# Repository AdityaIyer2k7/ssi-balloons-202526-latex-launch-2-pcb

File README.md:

# Stanford SSI Balloons; 2025-26 Latex Launch 2; PCB

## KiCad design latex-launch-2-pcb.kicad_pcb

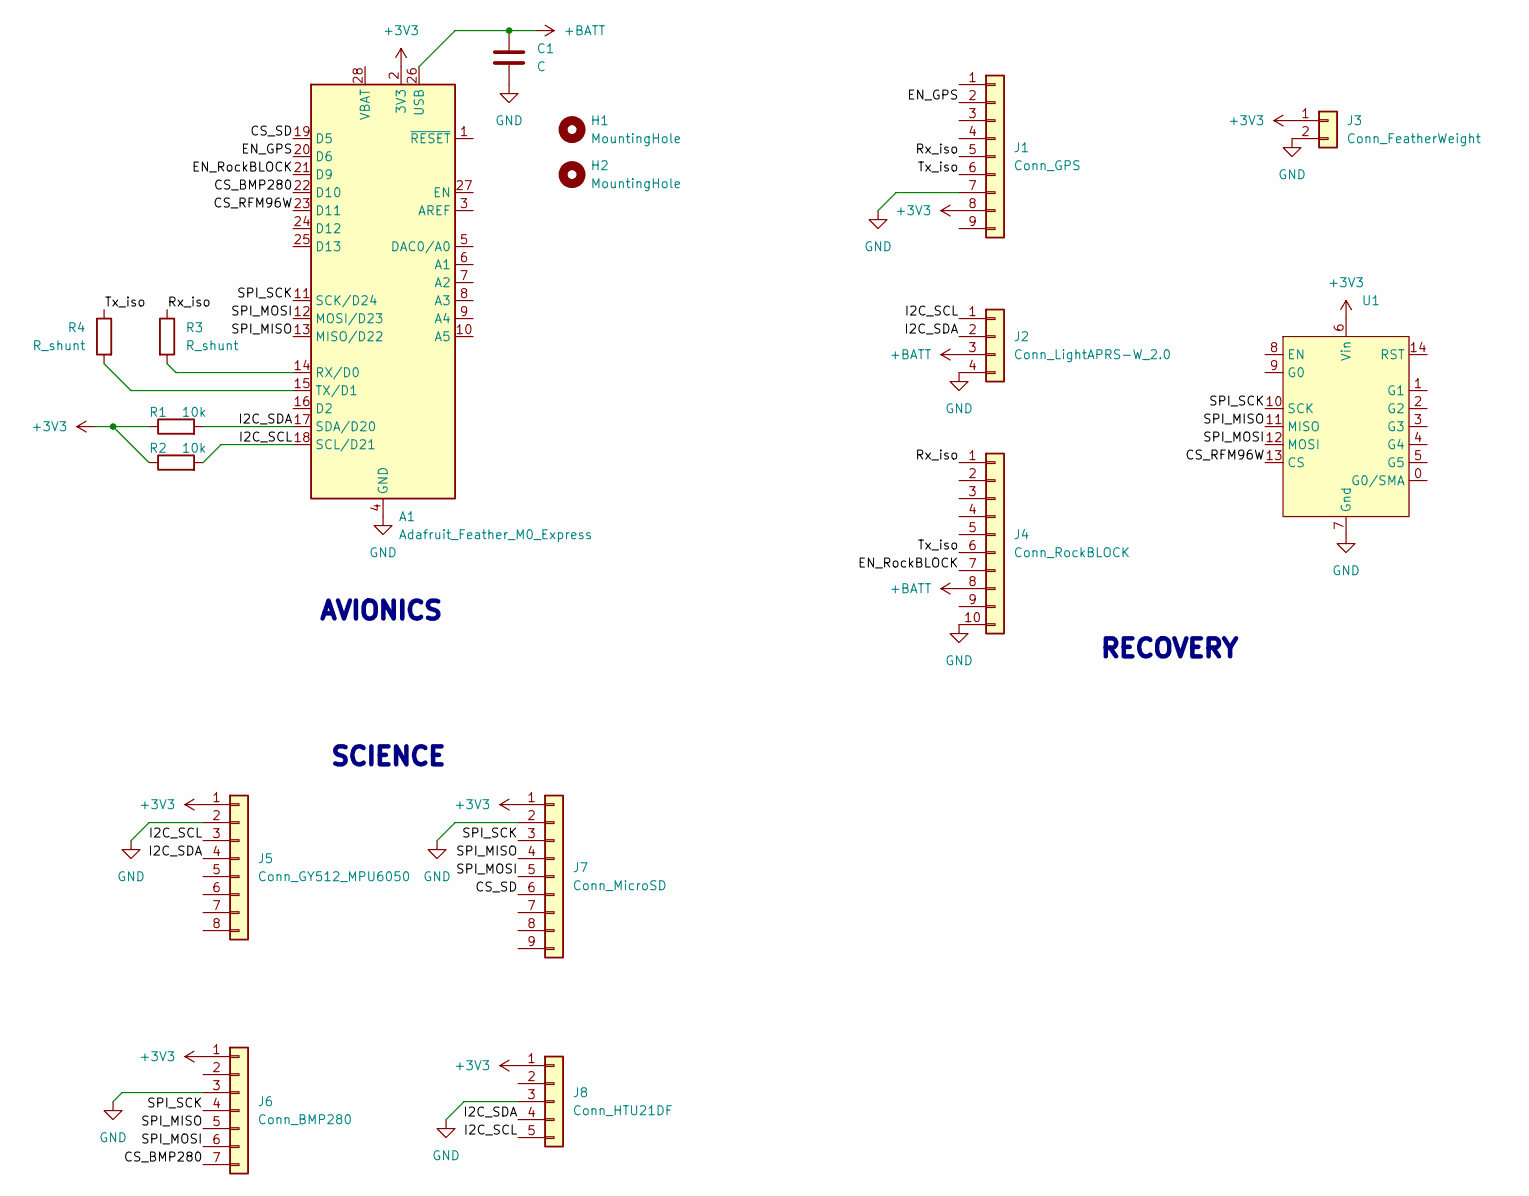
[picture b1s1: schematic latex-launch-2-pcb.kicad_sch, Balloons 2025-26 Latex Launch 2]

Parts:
A1: Adafruit_Feather_M0_Express; Adafruit_Feather_M0_RFM_WithMountingHoles
C1: C; C_Rect_L4.6mm_W2.0mm_P2.50mm_MKS02_FKP02
H1, H2: MountingHole; MountingHole_2.7mm_M2.5_ISO7380_Pad
J1: Conn_GPS; Adafruit_GPS_Breakout
J2: Conn_LightAPRS-W_2.0; JST_PH_S4B-PH-SM4-TB_1x04-1MP_P2.00mm_Horizontal
J3: Conn_FeatherWeight; JST_PH_S2B-PH-SM4-TB_1x02-1MP_P2.00mm_Horizontal
J4: Conn_RockBLOCK; Molex_PicoBlade_53047-1010_1x10_P1.25mm_Vertical
J5: Conn_GY512_MPU6050; GY-521 MPU6050
J6: Conn_BMP280; Adafruit_BMP280_Breakout
J7: Conn_MicroSD; Adafruit_MicroSD_Breakout
J8: Conn_HTU21DF; Adafruit_HTU21DF_Breakout
R1, R2: 10k; R_Axial_DIN0207_L6.3mm_D2.5mm_P10.16mm_Horizontal
R3, R4: R_shunt; PinHeader_1x02_P2.54mm_Vertical
U1: Adafruit_RFM96W_LoRa_Breakout

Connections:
+3V3: A1.2 (3V3), J1.8, J3.1, J5.1, J6.1, J7.1, J8.1, R1.1, R2.1, U1.6 (Vin)
+BATT: A1.26 (USB), C1.1, J2.3, J4.8
/CS_BMP280: A1.22 (D10), J6.7
/CS_RFM96W: A1.23 (D11), U1.13 (CS)
/CS_SD: A1.19 (D5), J7.6
/EN_GPS: A1.20 (D6), J1.2
/EN_RockBLOCK: A1.21 (D9), J4.7
/I2C_SCL: A1.18 (SCL/D21), J2.1, J5.3, J8.5, R2.2
/I2C_SDA: A1.17 (SDA/D20), J2.2, J5.4, J8.4, R1.2
/Rx_iso: J1.5, J4.1, R3.1
/SPI_MISO: A1.13 (MISO/D22), J6.5, J7.4, U1.11 (MISO)
/SPI_MOSI: A1.12 (MOSI/D23), J6.6, J7.5, U1.12 (MOSI)
/SPI_SCK: A1.11 (SCK/D24), J6.4, J7.3, U1.10 (SCK)
/Tx_iso: J1.6, J4.6, R4.1
GND: A1.4 (GND), C1.2, J1.7, J2.4, J3.2, J4.10, J5.2, J6.3, J7.2, J8.3, U1.7 (Gnd)
unnamed: A1.14 (RX/D0), R3.2
unnamed: A1.15 (TX/D1), R4.2

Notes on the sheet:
SCIENCE
AVIONICS
RECOVERY

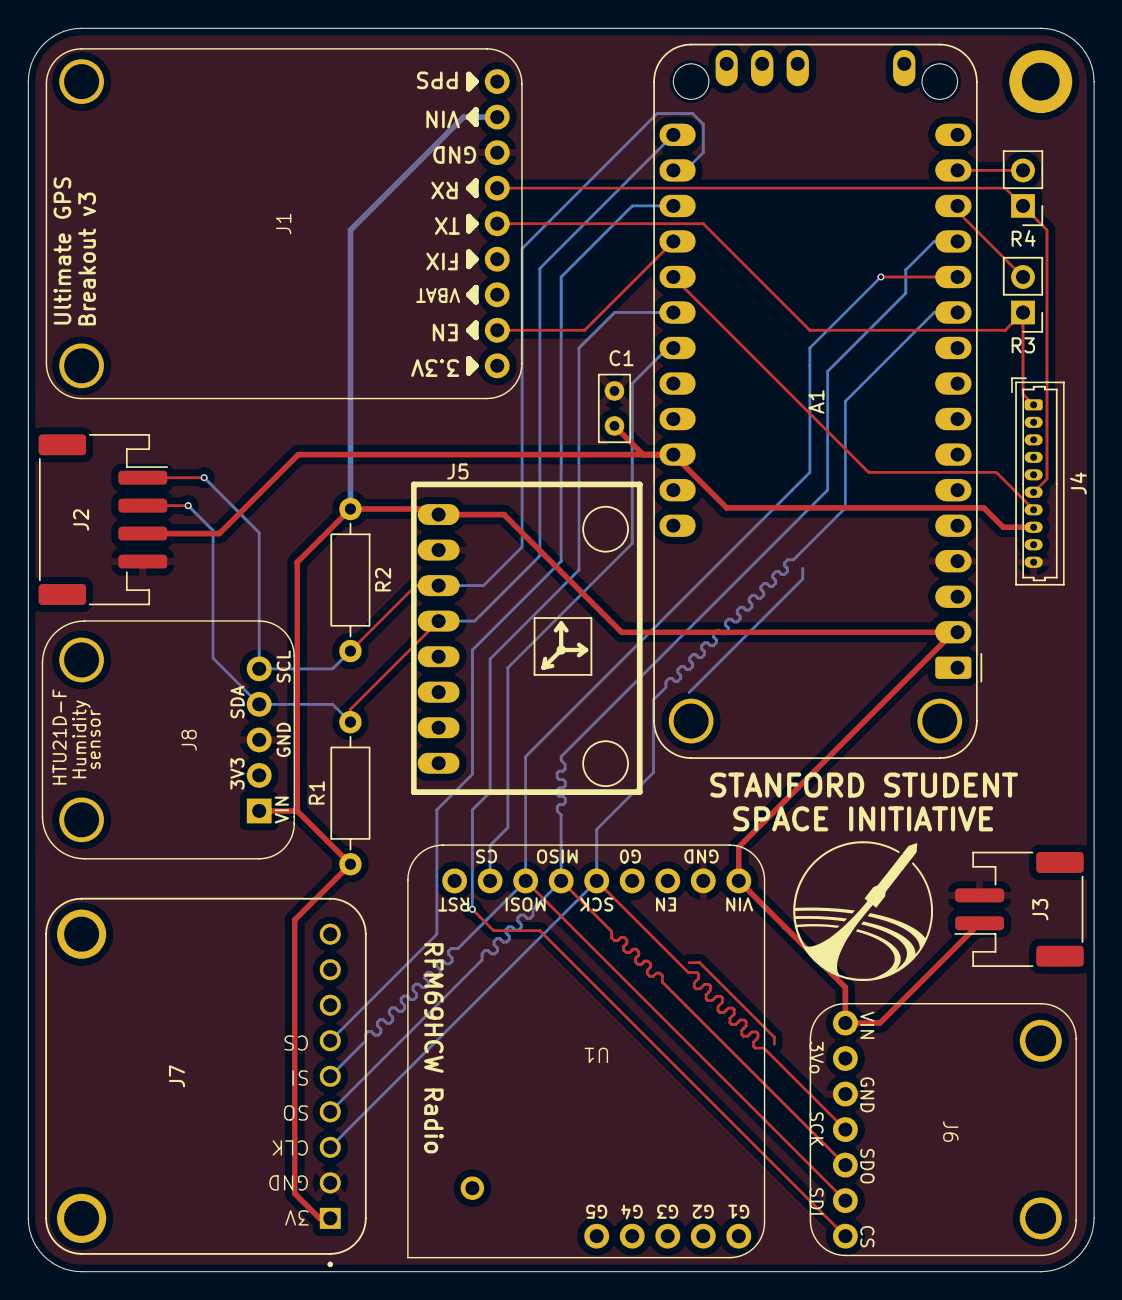
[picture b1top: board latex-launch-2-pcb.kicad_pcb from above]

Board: 4 copper layers, 76.2 x 88.9 mm, 16 parts (0 on the bottom side), 17 nets.

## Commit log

2025-11-08 Add README.md
2025-11-08 Add GNU GPL v3 license file
    Added the GNU General Public License version 3 to the project.
2025-11-08 Add .gitignore
2025-11-14 better pcb
2025-11-23 PCB version 2
2025-11-24 PCB v2 added mounting holes
2025-11-25 updated a lot
2025-12-22 Redid PCB; cleaner traces, design is 2 layers now
2025-12-22 Added logo, added groundplane on B.Cu
2025-12-23 Made changes as per design review
2025-12-23 2nd update
